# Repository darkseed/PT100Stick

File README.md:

# PT100Stick

[Interactive bom](http://htmlpreview.github.io/?https://github.com/RaymondHimle/PT100Stick/blob/master/Docs/ibom.html)

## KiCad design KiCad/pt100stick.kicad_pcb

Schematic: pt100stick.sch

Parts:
A1: Pololu_Breakout_A4988; Pololu_Breakout-16_15.2x20.3mm
C1, C2, C3: 0.1uF; C_0603_1608Metric_Pad1.05x0.95mm_HandSolder
FB1: Ferrite_Bead_Small; L_0603_1608Metric_Pad1.05x0.95mm_HandSolder
JP1: Cut for 4; SolderJumper-2_P1.3mm_Bridged_RoundedPad1.0x1.5mm
JP2: Cut for 3/4; SolderJumper-2_P1.3mm_Bridged_RoundedPad1.0x1.5mm
JP3: SolderJumper_3_Bridged12; SolderJumper-3_P1.3mm_Bridged12_RoundedPad1.0x1.5mm
R1: 430; R_0603_1608Metric_Pad1.05x0.95mm_HandSolder
U1: MAX31865ATP_; TQFN-20-1EP_5x5mm_P0.65mm_EP3.1x3.1mm; MPN MAX31865ATP+; Digi-Key_PN MAX31865ATP+-ND

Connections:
+3V3: A1.2 (VDD), C2.1, FB1.1, U1.19 (DVDD)
/BIAS: R1.2, U1.1 (BIAS), U1.2 (REFIN+)
/CS: A1.12 (MS3), U1.13 (~CS)
/FORCE2: JP3.2 (C), U1.6 (FORCE2)
/FORCE+: A1.3 (1B), JP2.1 (A), U1.5 (FORCE+)
/FORCE-: A1.6 (2B), JP1.1 (A), U1.9 (FORCE-)
/MISO: A1.10 (MS1), U1.11 (SDI)
/MOSI: A1.13 (~RESET), A1.14 (~SLEEP), U1.14 (SDO)
/RTDIN+: A1.4 (1A), C1.1, JP2.2 (B), JP3.3 (B), U1.7 (RTDIN+)
/RTDIN-: A1.5 (2A), C1.2, JP1.2 (B), U1.8 (RTDIN-)
/SCK: A1.11 (MS2), U1.12 (SCLK)
GND: A1.7 (GND), C2.2, C3.2, JP3.1 (A), U1.10 (GND2), U1.15 (DGND), U1.16 (GND1), U1.21 (GND/PAD)
unnamed: R1.1, U1.3 (REFIM-), U1.4 (ISENSOR)
VDDA: C3.1, FB1.2, U1.20 (VDD)

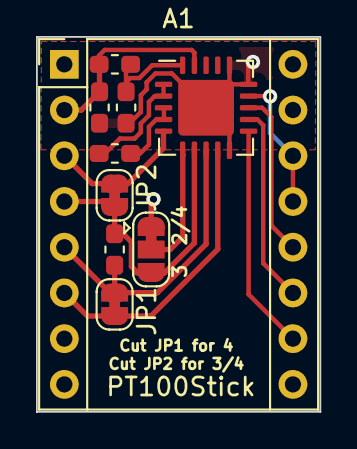
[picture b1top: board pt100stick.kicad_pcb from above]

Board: 2 copper layers, 15.7 x 20.8 mm, 10 parts (0 on the bottom side), 14 nets.

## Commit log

2020-05-12 initial
2020-05-12 removeold
2020-05-13 Start Project Lib / Relayout
2020-05-13 Moved all footprints to project lib (I think)
2020-05-13 Fix silkscreen issue
2020-05-13 Fix more silkscreen, gen gerbers
2020-05-14 Reworked layout
2020-05-30 Commiting before final changes (need to swap miso and mosi)
2020-05-30 Hopefully stable release :D
2020-06-23 Quick fixes
2020-06-23 fix logo
2020-06-23 Change top flood fill
2020-06-24 update docs
2020-06-24 can't type
2020-06-24 Slight tweaks
2020-07-09 enlarge holes

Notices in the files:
KiCad/pt100stick.kicad_pcb:
licensed under GPL3
